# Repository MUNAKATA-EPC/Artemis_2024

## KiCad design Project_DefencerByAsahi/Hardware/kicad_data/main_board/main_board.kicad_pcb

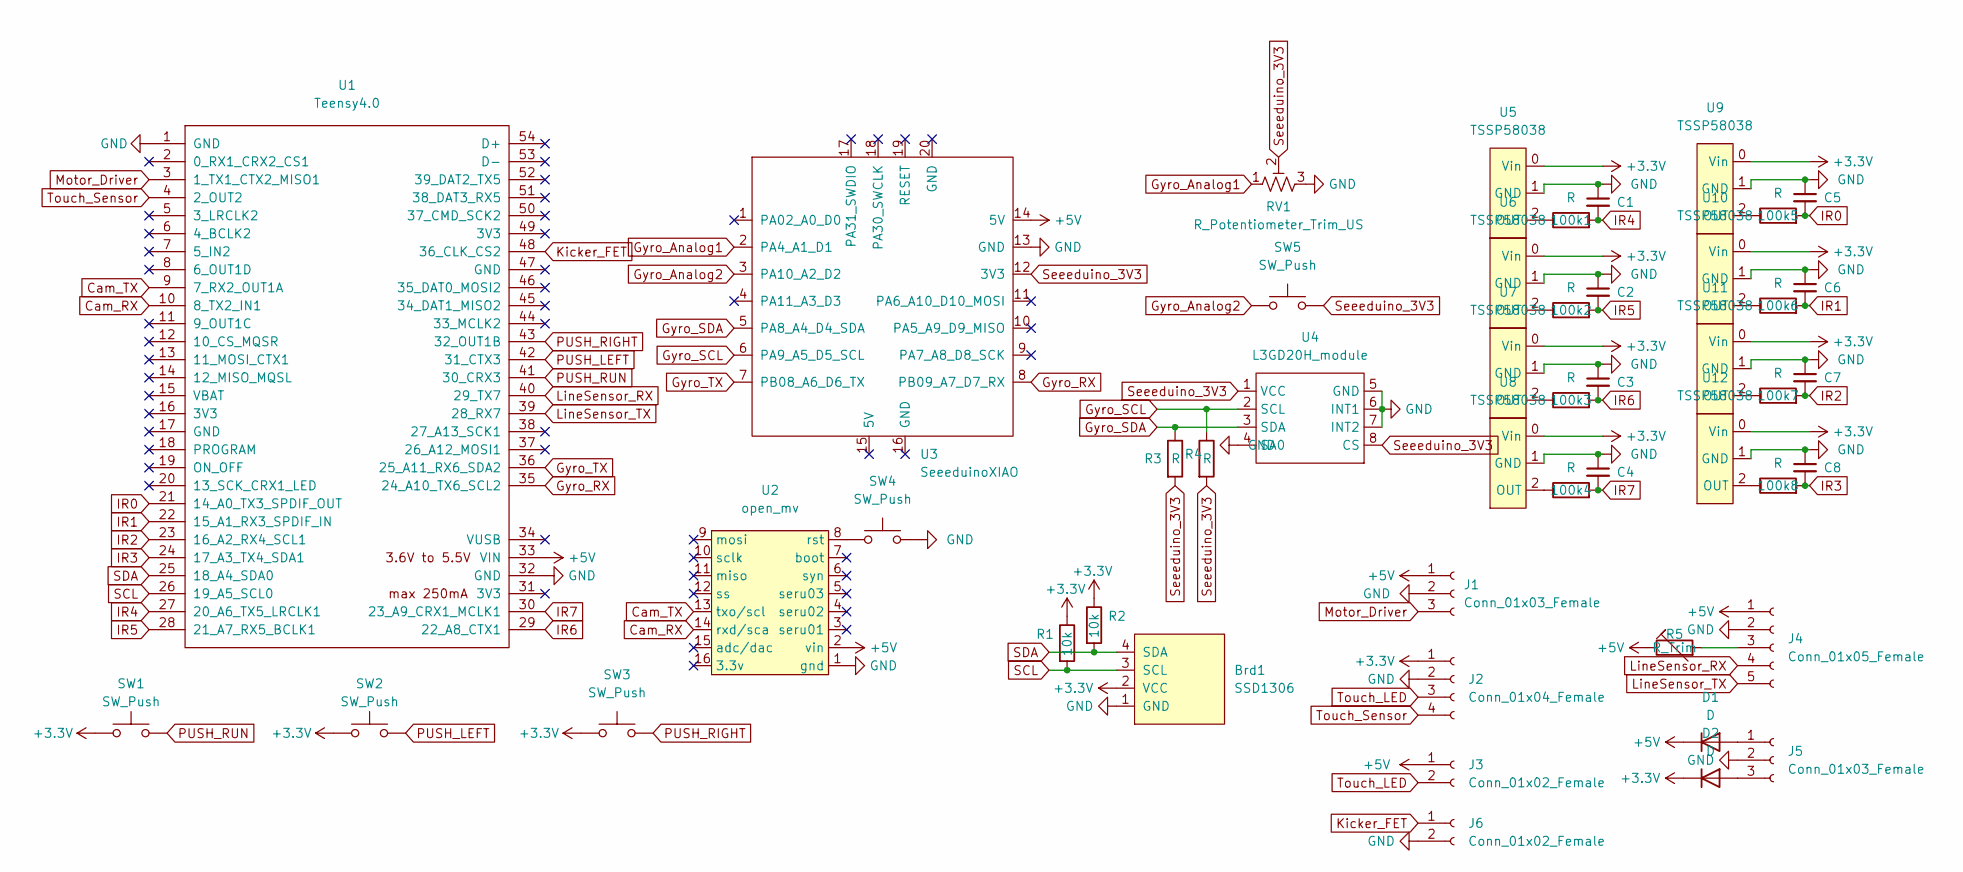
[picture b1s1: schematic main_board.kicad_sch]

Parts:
100k1, 100k2, 100k3, 100k4, 100k5, 100k6, 100k7, 100k8: R; R_Axial_DIN0204_L3.6mm_D1.6mm_P5.08mm_Horizontal
Brd1: SSD1306; 128x64OLED
C1, C2, C3, C4, C5, C6, C7, C8: C_Small; C_Disc_D3.0mm_W2.0mm_P2.50mm
D1, D2: D; D_A-405_P7.62mm_Horizontal
J1, J5: Conn_01x03_Female; JST_XH_B3B-XH-A_1x03_P2.50mm_Vertical
J2: Conn_01x04_Female; JST_XH_B4B-XH-A_1x04_P2.50mm_Vertical
J3, J6: Conn_01x02_Female; JST_XH_B2B-XH-A_1x02_P2.50mm_Vertical
J4: Conn_01x05_Female; JST_XH_B5B-XH-A_1x05_P2.50mm_Vertical
R1, R2: 10k; R_Axial_DIN0204_L3.6mm_D1.6mm_P5.08mm_Horizontal
R3, R4: R; R_Axial_DIN0204_L3.6mm_D1.6mm_P5.08mm_Horizontal
R5: R_Trim; R_Varlable
RV1: R_Potentiometer_Trim_US; R_Varlable
SW1, SW2, SW3, SW4, SW5: SW_Push; SW_PUSH_6mm_H5mm
U1: Teensy4.0; Teensy_Brakeout
U2: open_mv; OpenMV
U3: SeeeduinoXIAO; seeeduinoXIAO
U4: L3GD20H_module; L3GD20H_Module_KiCad6.0
U5, U6, U7, U8, U9, U10, U11, U12: TSSP58038

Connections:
+3.3V: Brd1.2 (VCC), D2.1 (K), J2.1, R1.1, R2.1, SW1.1, SW2.1, SW3.1, U5.0 (Vin), U6.0 (Vin), U7.0 (Vin), U8.0 (Vin), U9.0 (Vin), U10.0 (Vin), U11.0 (Vin), U12.0 (Vin)
+5V: D1.1 (K), J1.1, J3.1, J4.1, R5.1, U1.33 (VIN), U2.2 (vin), U3.14 (5V)
Cam_RX: U1.10 (8_TX2_IN1), U2.14 (rxd/sca)
Cam_TX: U1.9 (7_RX2_OUT1A), U2.13 (txo/scl)
GND: Brd1.1 (GND), C1.1, C2.1, C3.1, C4.1, C5.1, C6.1, C7.1, C8.1, J1.2, J2.2, J4.2, J5.2, J6.2, RV1.3, SW4.2, U1.1 (GND), U1.32 (GND), U2.1 (gnd), U3.13 (GND), U4.4 (SA0), U4.5 (GND), U4.6 (INT1), U4.7 (INT2), U5.1 (GND), U6.1 (GND), U7.1 (GND), U8.1 (GND), U9.1 (GND), U10.1 (GND), U11.1 (GND), U12.1 (GND)
Gyro_Analog1: RV1.1, U3.2 (PA4_A1_D1)
Gyro_Analog2: SW5.1, U3.3 (PA10_A2_D2)
Gyro_RX: U1.35 (24_A10_TX6_SCL2), U3.8 (PB09_A7_D7_RX)
Gyro_SCL: R4.1, U3.6 (PA9_A5_D5_SCL), U4.2 (SCL)
Gyro_SDA: R3.1, U3.5 (PA8_A4_D4_SDA), U4.3 (SDA)
Gyro_TX: U1.36 (25_A11_RX6_SDA2), U3.7 (PB08_A6_D6_TX)
IR0: 100k5.2, C5.2, U1.21 (14_A0_TX3_SPDIF_OUT)
IR1: 100k6.2, C6.2, U1.22 (15_A1_RX3_SPDIF_IN)
IR2: 100k7.2, C7.2, U1.23 (16_A2_RX4_SCL1)
IR3: 100k8.2, C8.2, U1.24 (17_A3_TX4_SDA1)
IR4: 100k1.2, C1.2, U1.27 (20_A6_TX5_LRCLK1)
IR5: 100k2.2, C2.2, U1.28 (21_A7_RX5_BCLK1)
IR6: 100k3.2, C3.2, U1.29 (22_A8_CTX1)
IR7: 100k4.2, C4.2, U1.30 (23_A9_CRX1_MCLK1)
Kicker_FET: J6.1, U1.48 (36_CLK_CS2)
LineSensor_RX: J4.4, U1.40 (29_TX7)
LineSensor_TX: J4.5, U1.39 (28_RX7)
Motor_Driver: J1.3, U1.3 (1_TX1_CTX2_MISO1)
unnamed: 100k1.1, U5.2 (OUT)
unnamed: 100k2.1, U6.2 (OUT)
unnamed: 100k3.1, U7.2 (OUT)
unnamed: 100k4.1, U8.2 (OUT)
unnamed: 100k5.1, U9.2 (OUT)
unnamed: 100k6.1, U10.2 (OUT)
unnamed: 100k7.1, U11.2 (OUT)
unnamed: 100k8.1, U12.2 (OUT)
unnamed: D1.2 (A), J5.1
unnamed: D2.2 (A), J5.3
unnamed: J4.3, R5.2
unnamed: SW4.1, U2.8 (rst)
PUSH_LEFT: SW2.2, U1.42 (31_CTX3)
PUSH_RIGHT: SW3.2, U1.43 (32_OUT1B)
PUSH_RUN: SW1.2, U1.41 (30_CRX3)
SCL: Brd1.3 (SCL), R1.2, U1.26 (19_A5_SCL0)
SDA: Brd1.4 (SDA), R2.2, U1.25 (18_A4_SDA0)
Seeeduino_3V3: R3.2, R4.2, RV1.2, SW5.2, U3.12 (3V3), U4.1 (VCC), U4.8 (CS)
Touch_LED: J2.3, J3.2
Touch_Sensor: J2.4, U1.4 (2_OUT2)

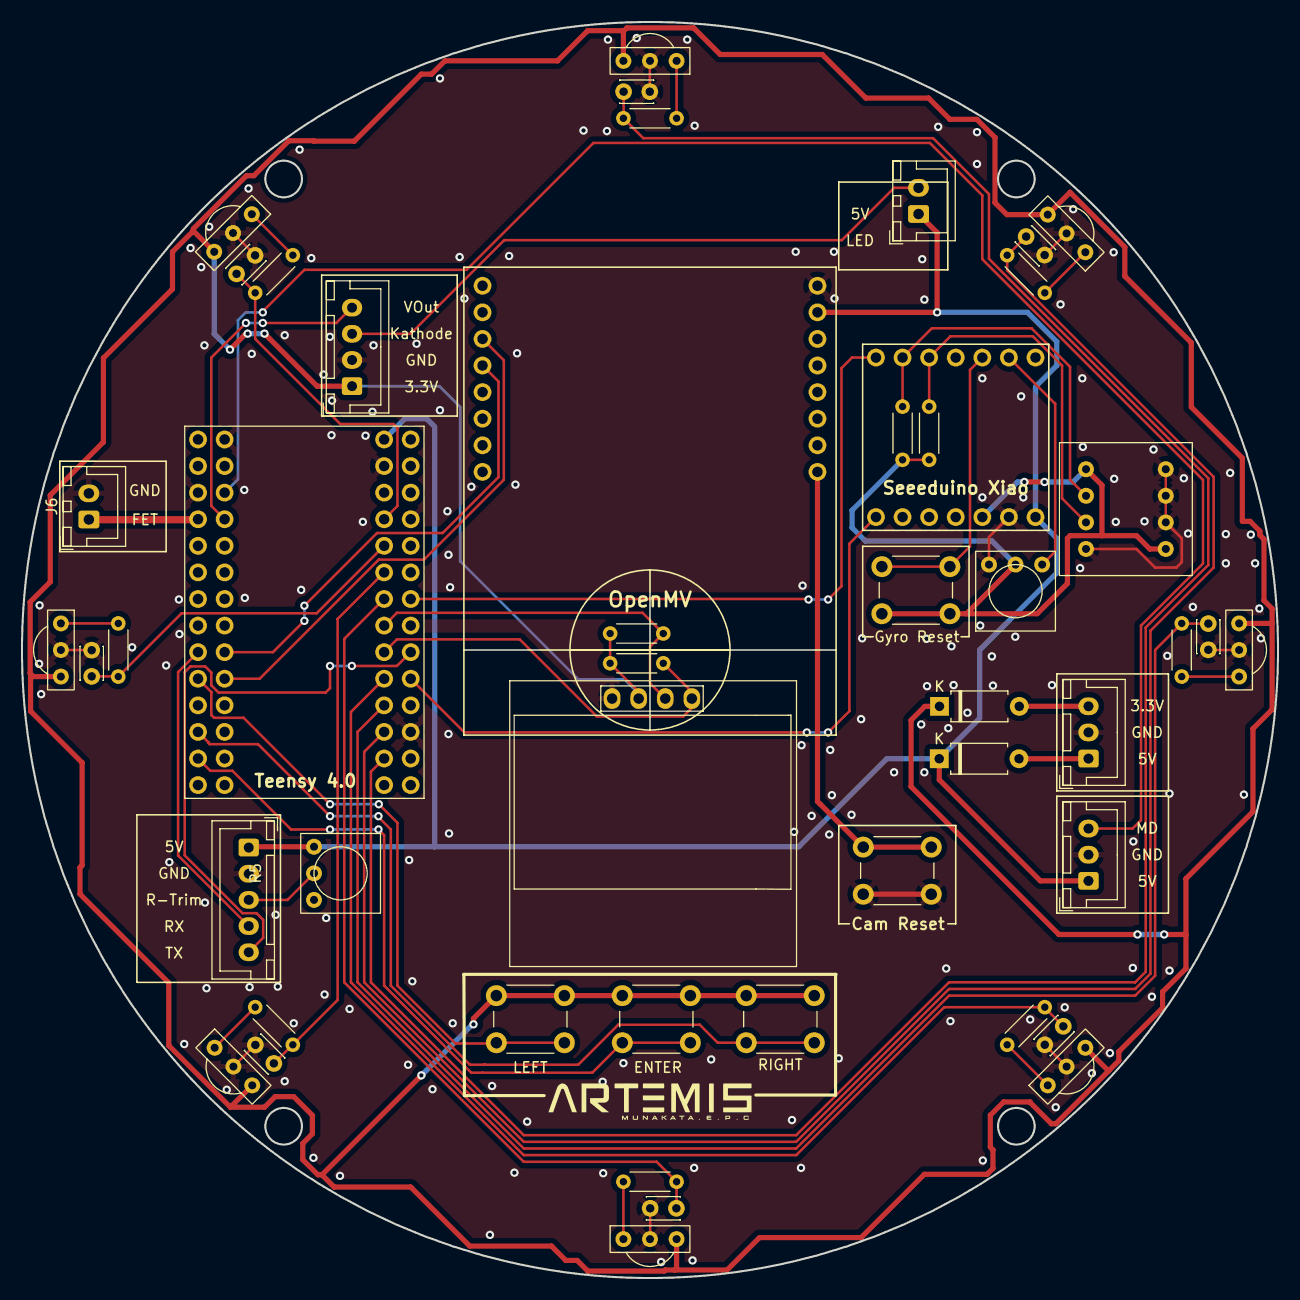
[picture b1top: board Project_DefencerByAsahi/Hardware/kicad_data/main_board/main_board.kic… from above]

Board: 2 copper layers, 120.0 x 120.0 mm, 48 parts (0 on the bottom side), 43 nets.

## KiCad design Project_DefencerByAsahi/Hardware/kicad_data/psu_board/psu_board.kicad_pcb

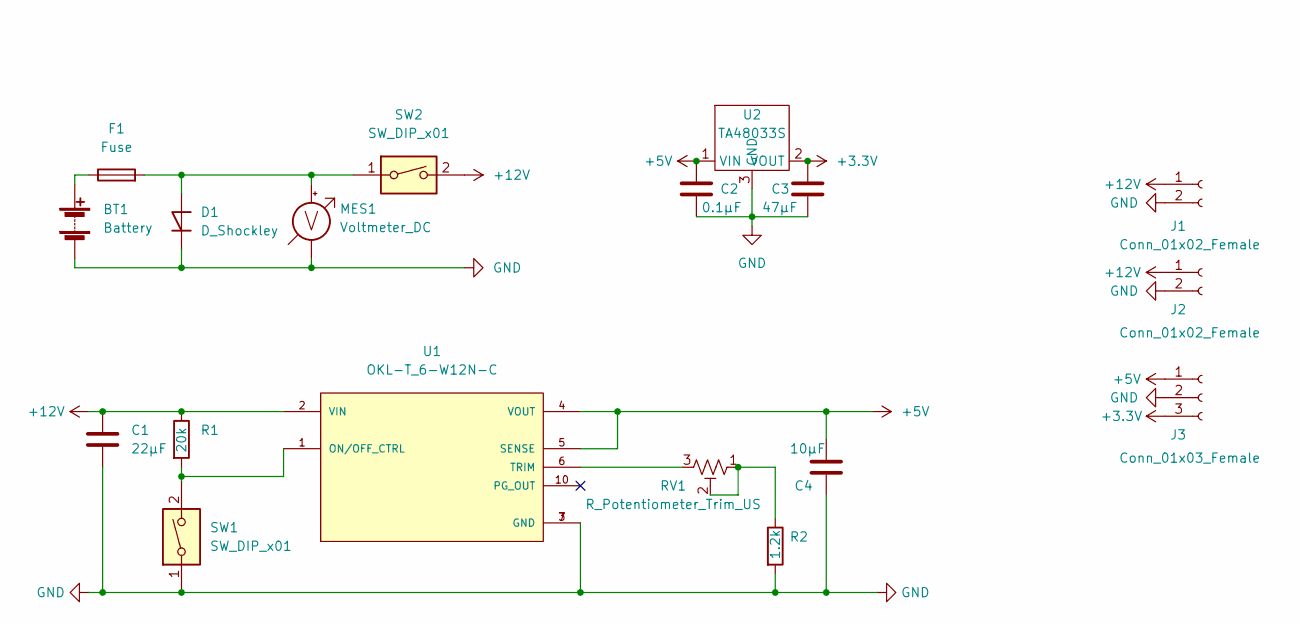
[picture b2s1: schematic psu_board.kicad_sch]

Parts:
BT1: Battery; JST_VH_B2P-VH-B_1x02_P3.96mm_Vertical
C1: 22μF; C_Disc_D5.1mm_W3.2mm_P5.00mm
C2: 0.1μF; C_Disc_D3.0mm_W1.6mm_P2.50mm
C3: 47μF; C_Radial_D6.3mm_H11.0mm_P2.50mm
C4: 10μF; C_Disc_D5.1mm_W3.2mm_P5.00mm
D1: D_Shockley; D_5W_P12.70mm_Horizontal
F1: Fuse; fuse_socket
J1, J2: Conn_01x02_Female; JST_XH_B2B-XH-A_1x02_P2.50mm_Vertical
J3: Conn_01x03_Female; JST_XH_B3B-XH-A_1x03_P2.50mm_Vertical
MES1: Voltmeter_DC; voltage_counter
R1: 20k; R_Axial_DIN0204_L3.6mm_D1.6mm_P5.08mm_Horizontal
R2: 1.2k; R_Axial_DIN0204_L3.6mm_D1.6mm_P5.08mm_Horizontal
RV1: R_Potentiometer_Trim_US; Potentiometer_Bourns_3296W_Vertical
SW1, SW2: SW_DIP_x01; DS-850k
U1: OKL-T_6-W12N-C; DCDC-murata-6A
U2: TA48033S

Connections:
+3.3V: C3.1, J3.3, U2.2 (VOUT)
+5V: C2.1, C4.1, J3.1, U1.4 (VOUT), U1.5 (SENSE), U2.1 (VIN)
+12V: C1.1, J1.1, J2.1, R1.1, SW2.2, U1.2 (VIN)
GND: BT1.2 (-), C1.2, C2.2, C3.2, C4.2, D1.1 (K), J1.2, J2.2, J3.2, MES1.1 (-), R2.2, SW1.1, U1.3 (GND), U1.7 (GND), U2.3 (GND)
unnamed: BT1.1 (+), F1.1
unnamed: D1.2 (A), F1.2, MES1.2 (+), SW2.1
unnamed: R1.2, SW1.2, U1.1 (ON/OFF_CTRL)
unnamed: R2.1, RV1.1, RV1.2
unnamed: RV1.3, U1.6 (TRIM)

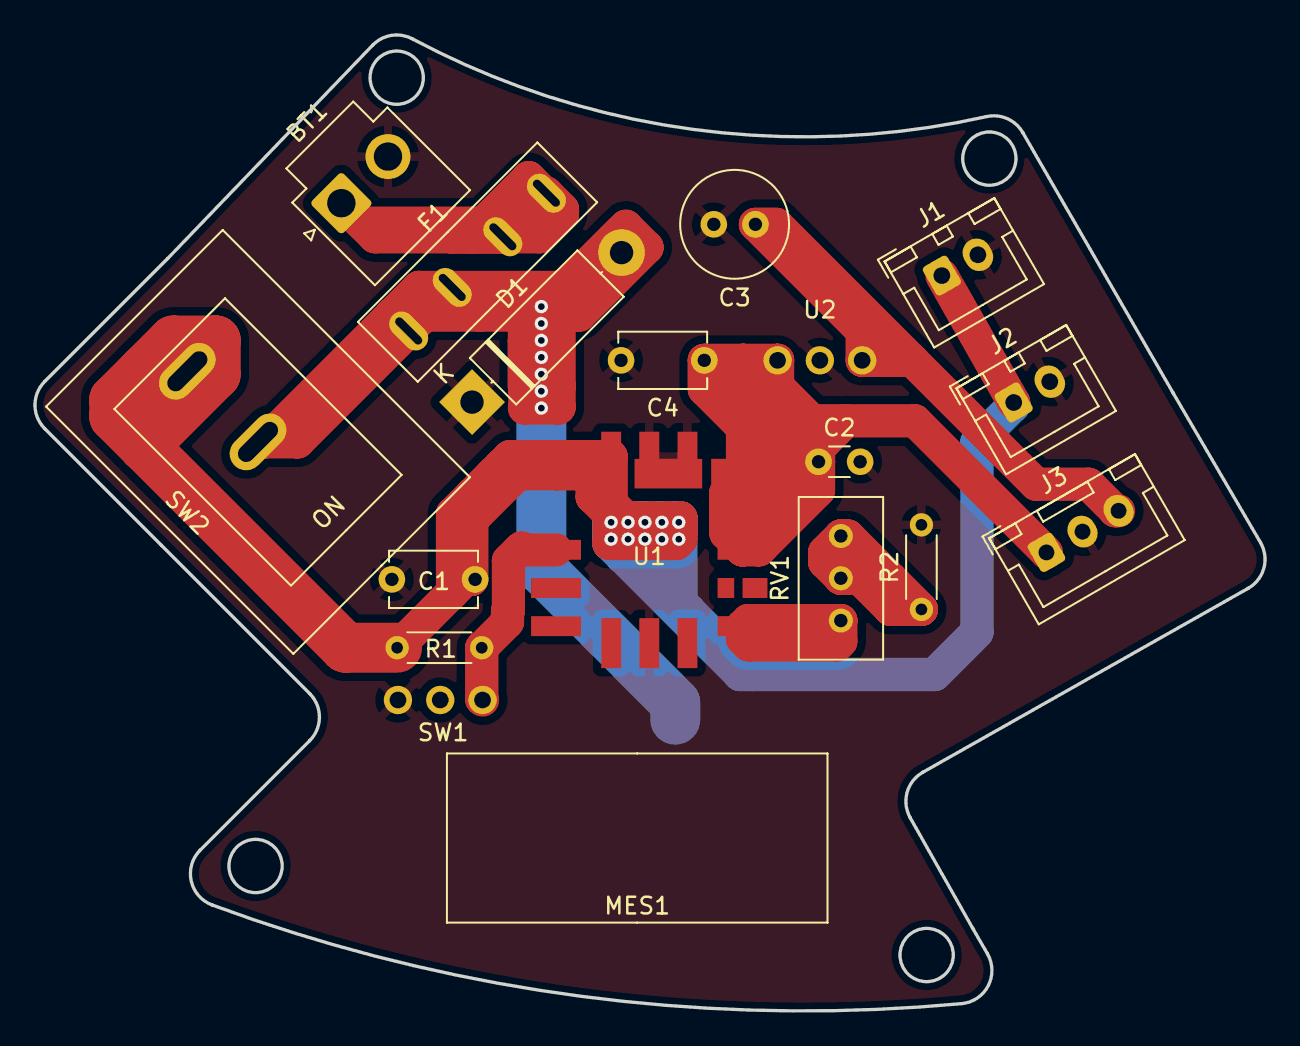
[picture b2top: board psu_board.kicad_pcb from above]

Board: 2 copper layers, 73.9 x 58.6 mm, 18 parts (0 on the bottom side), 9 nets.

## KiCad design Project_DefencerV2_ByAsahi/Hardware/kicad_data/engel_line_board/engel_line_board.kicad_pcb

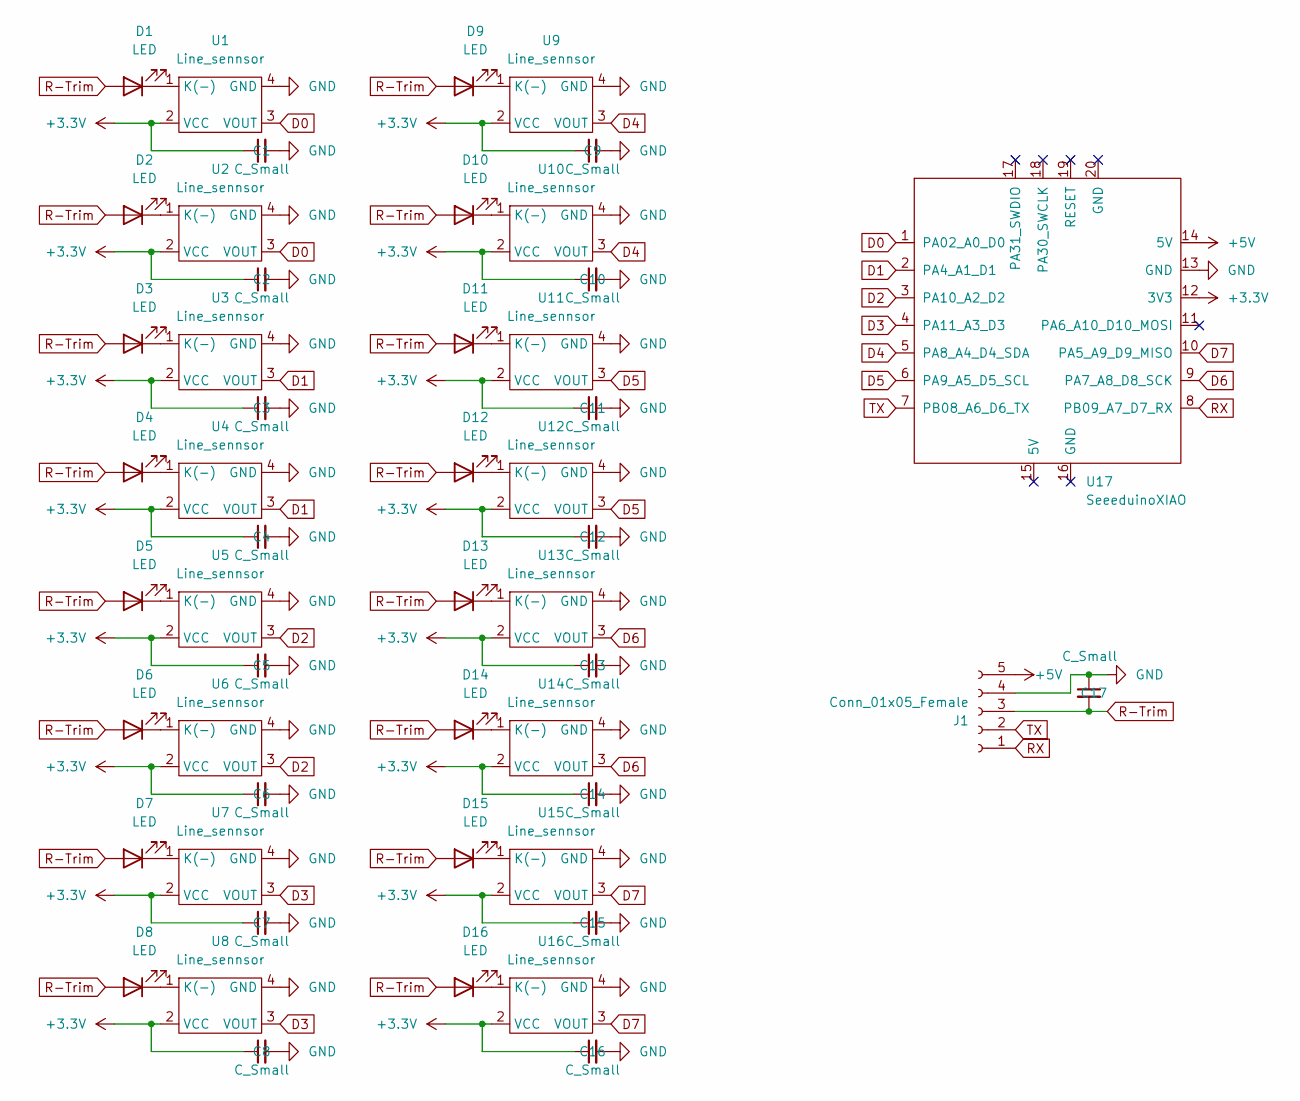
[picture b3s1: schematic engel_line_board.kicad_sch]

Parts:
C1, C2, C3, C4, C5, C6, C7, C8, C9, C10, C11, C12, C13, C14, C15, C16, C17: C_Small; C_Disc_D3.8mm_W2.6mm_P2.50mm
D1, D2, D3, D4, D5, D6, D7, D8, D9, D10, D11, D12, D13, D14, D15, D16: LED; LED_D3.0mm_Clear
J1: Conn_01x05_Female; JST_XH_S5B-XH-A_1x05_P2.50mm_Horizontal
U1, U2, U3, U4, U5, U6, U7, U8, U9, U10, U11, U12, U13, U14, U15, U16: Line_sennsor; Line_Sensor
U17: SeeeduinoXIAO; seeeduinoXIAO

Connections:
+3.3V: C1.1, C2.1, C3.1, C4.1, C5.1, C6.1, C7.1, C8.1, C9.1, C10.1, C11.1, C12.1, C13.1, C14.1, C15.1, C16.1, U1.2 (VCC), U2.2 (VCC), U3.2 (VCC), U4.2 (VCC), U5.2 (VCC), U6.2 (VCC), U7.2 (VCC), U8.2 (VCC), U9.2 (VCC), U10.2 (VCC), U11.2 (VCC), U12.2 (VCC), U13.2 (VCC), U14.2 (VCC), U15.2 (VCC), U16.2 (VCC), U17.12 (3V3)
+5V: J1.5, U17.14 (5V)
D0: U1.3 (VOUT), U2.3 (VOUT), U17.1 (PA02_A0_D0)
D1: U3.3 (VOUT), U4.3 (VOUT), U17.2 (PA4_A1_D1)
D2: U5.3 (VOUT), U6.3 (VOUT), U17.3 (PA10_A2_D2)
D3: U7.3 (VOUT), U8.3 (VOUT), U17.4 (PA11_A3_D3)
D4: U9.3 (VOUT), U10.3 (VOUT), U17.5 (PA8_A4_D4_SDA)
D5: U11.3 (VOUT), U12.3 (VOUT), U17.6 (PA9_A5_D5_SCL)
D6: U13.3 (VOUT), U14.3 (VOUT), U17.9 (PA7_A8_D8_SCK)
D7: U15.3 (VOUT), U16.3 (VOUT), U17.10 (PA5_A9_D9_MISO)
GND: C1.2, C2.2, C3.2, C4.2, C5.2, C6.2, C7.2, C8.2, C9.2, C10.2, C11.2, C12.2, C13.2, C14.2, C15.2, C16.2, C17.1, J1.4, U1.4 (GND), U2.4 (GND), U3.4 (GND), U4.4 (GND), U5.4 (GND), U6.4 (GND), U7.4 (GND), U8.4 (GND), U9.4 (GND), U10.4 (GND), U11.4 (GND), U12.4 (GND), U13.4 (GND), U14.4 (GND), U15.4 (GND), U16.4 (GND), U17.13 (GND)
unnamed: D1.1 (K), U1.1 (K(-))
unnamed: D2.1 (K), U2.1 (K(-))
unnamed: D3.1 (K), U3.1 (K(-))
unnamed: D4.1 (K), U4.1 (K(-))
unnamed: D5.1 (K), U5.1 (K(-))
unnamed: D6.1 (K), U6.1 (K(-))
unnamed: D7.1 (K), U7.1 (K(-))
unnamed: D8.1 (K), U8.1 (K(-))
unnamed: D9.1 (K), U9.1 (K(-))
unnamed: D10.1 (K), U10.1 (K(-))
unnamed: D11.1 (K), U11.1 (K(-))
unnamed: D12.1 (K), U12.1 (K(-))
unnamed: D13.1 (K), U13.1 (K(-))
unnamed: D14.1 (K), U14.1 (K(-))
unnamed: D15.1 (K), U15.1 (K(-))
unnamed: D16.1 (K), U16.1 (K(-))
R-Trim: C17.2, D1.2 (A), D2.2 (A), D3.2 (A), D4.2 (A), D5.2 (A), D6.2 (A), D7.2 (A), D8.2 (A), D9.2 (A), D10.2 (A), D11.2 (A), D12.2 (A), D13.2 (A), D14.2 (A), D15.2 (A), D16.2 (A), J1.3
RX: J1.1, U17.8 (PB09_A7_D7_RX)
TX: J1.2, U17.7 (PB08_A6_D6_TX)

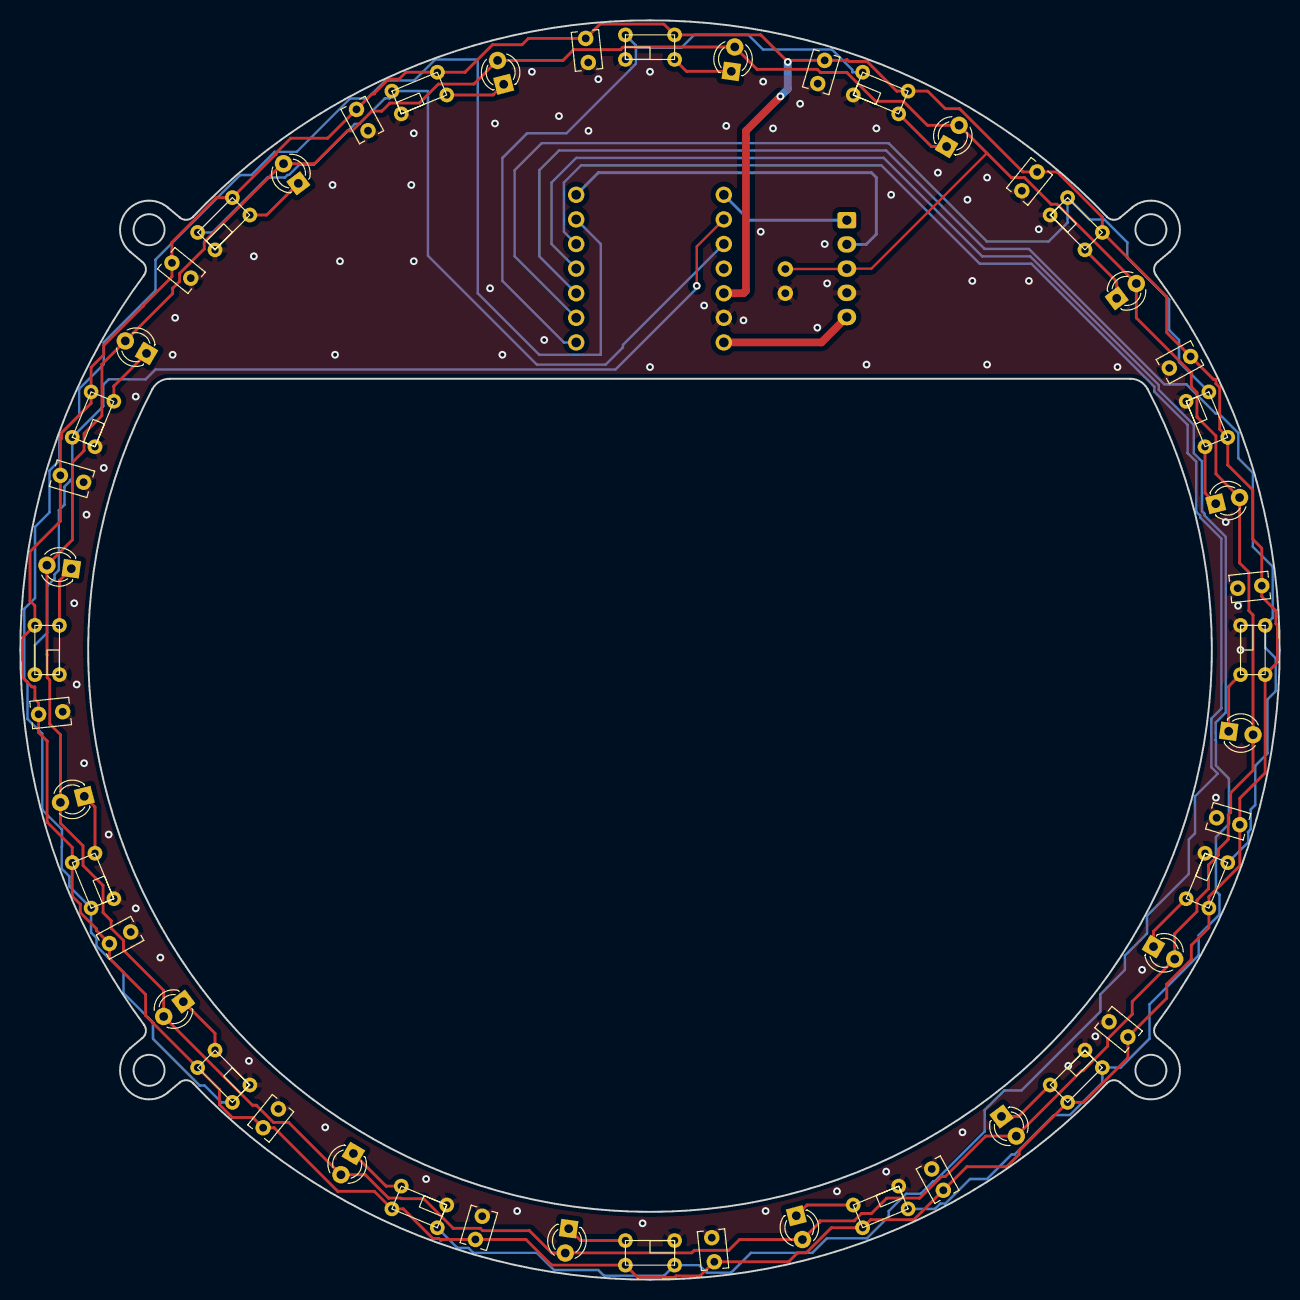
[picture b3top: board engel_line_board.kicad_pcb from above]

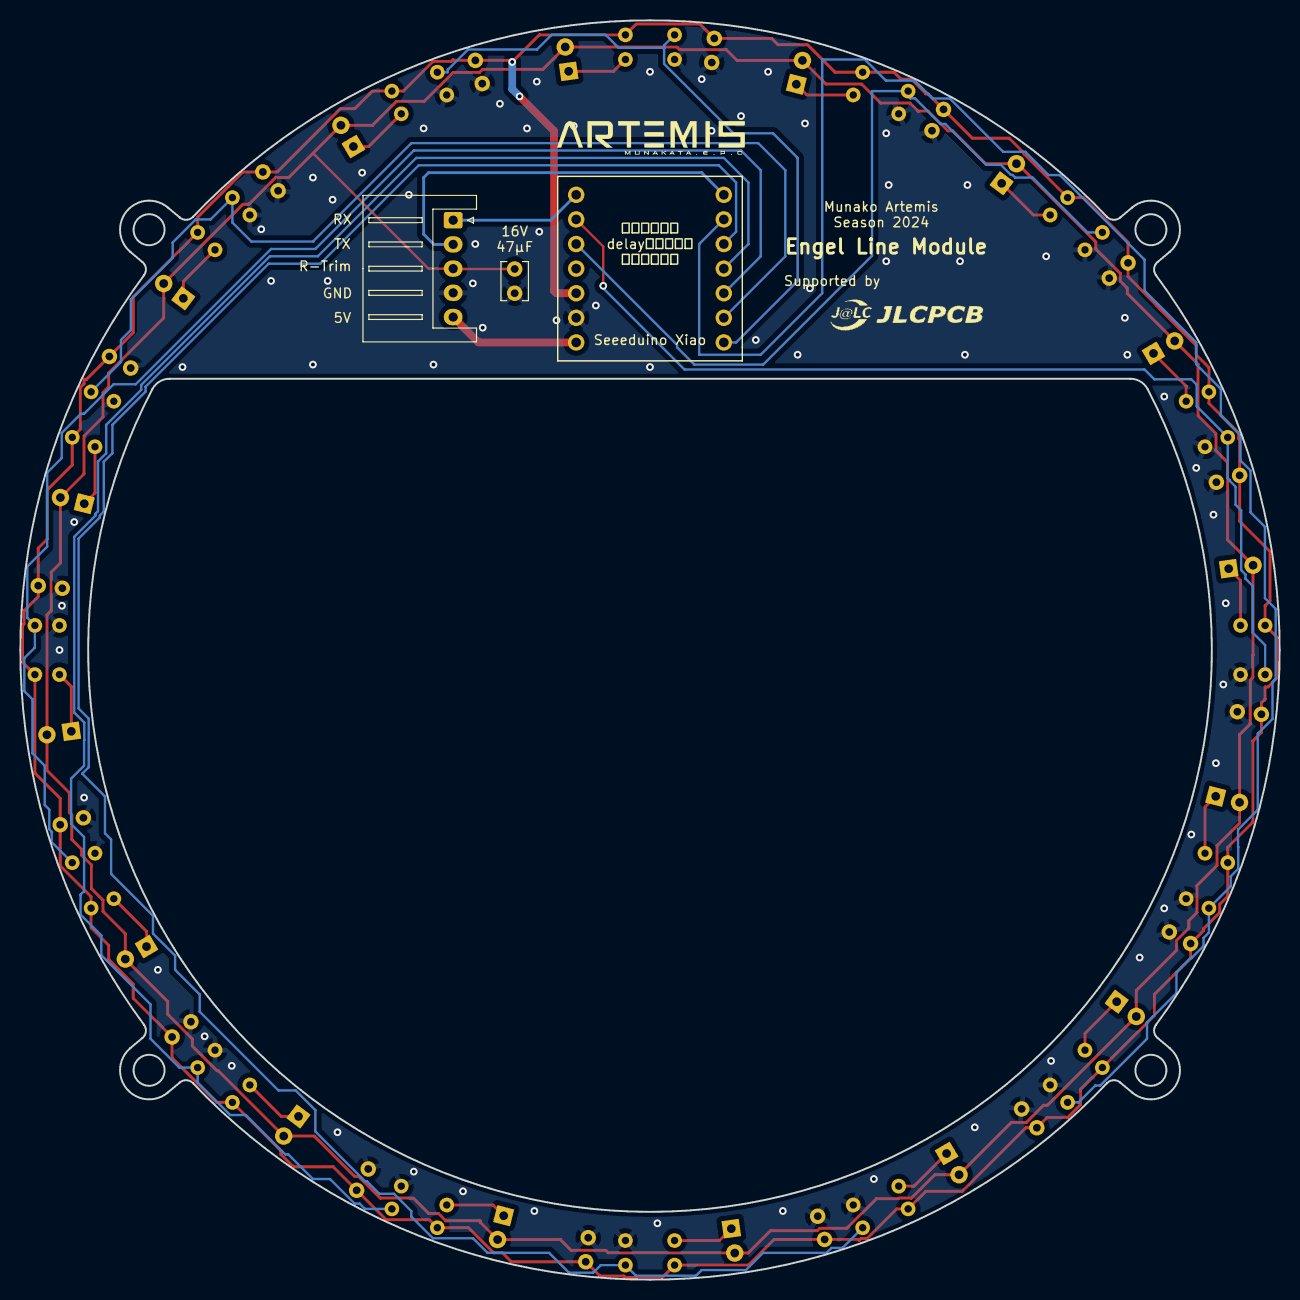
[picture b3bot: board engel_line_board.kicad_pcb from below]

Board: 2 copper layers, 130.0 x 130.0 mm, 51 parts (3 on the bottom side), 30 nets.

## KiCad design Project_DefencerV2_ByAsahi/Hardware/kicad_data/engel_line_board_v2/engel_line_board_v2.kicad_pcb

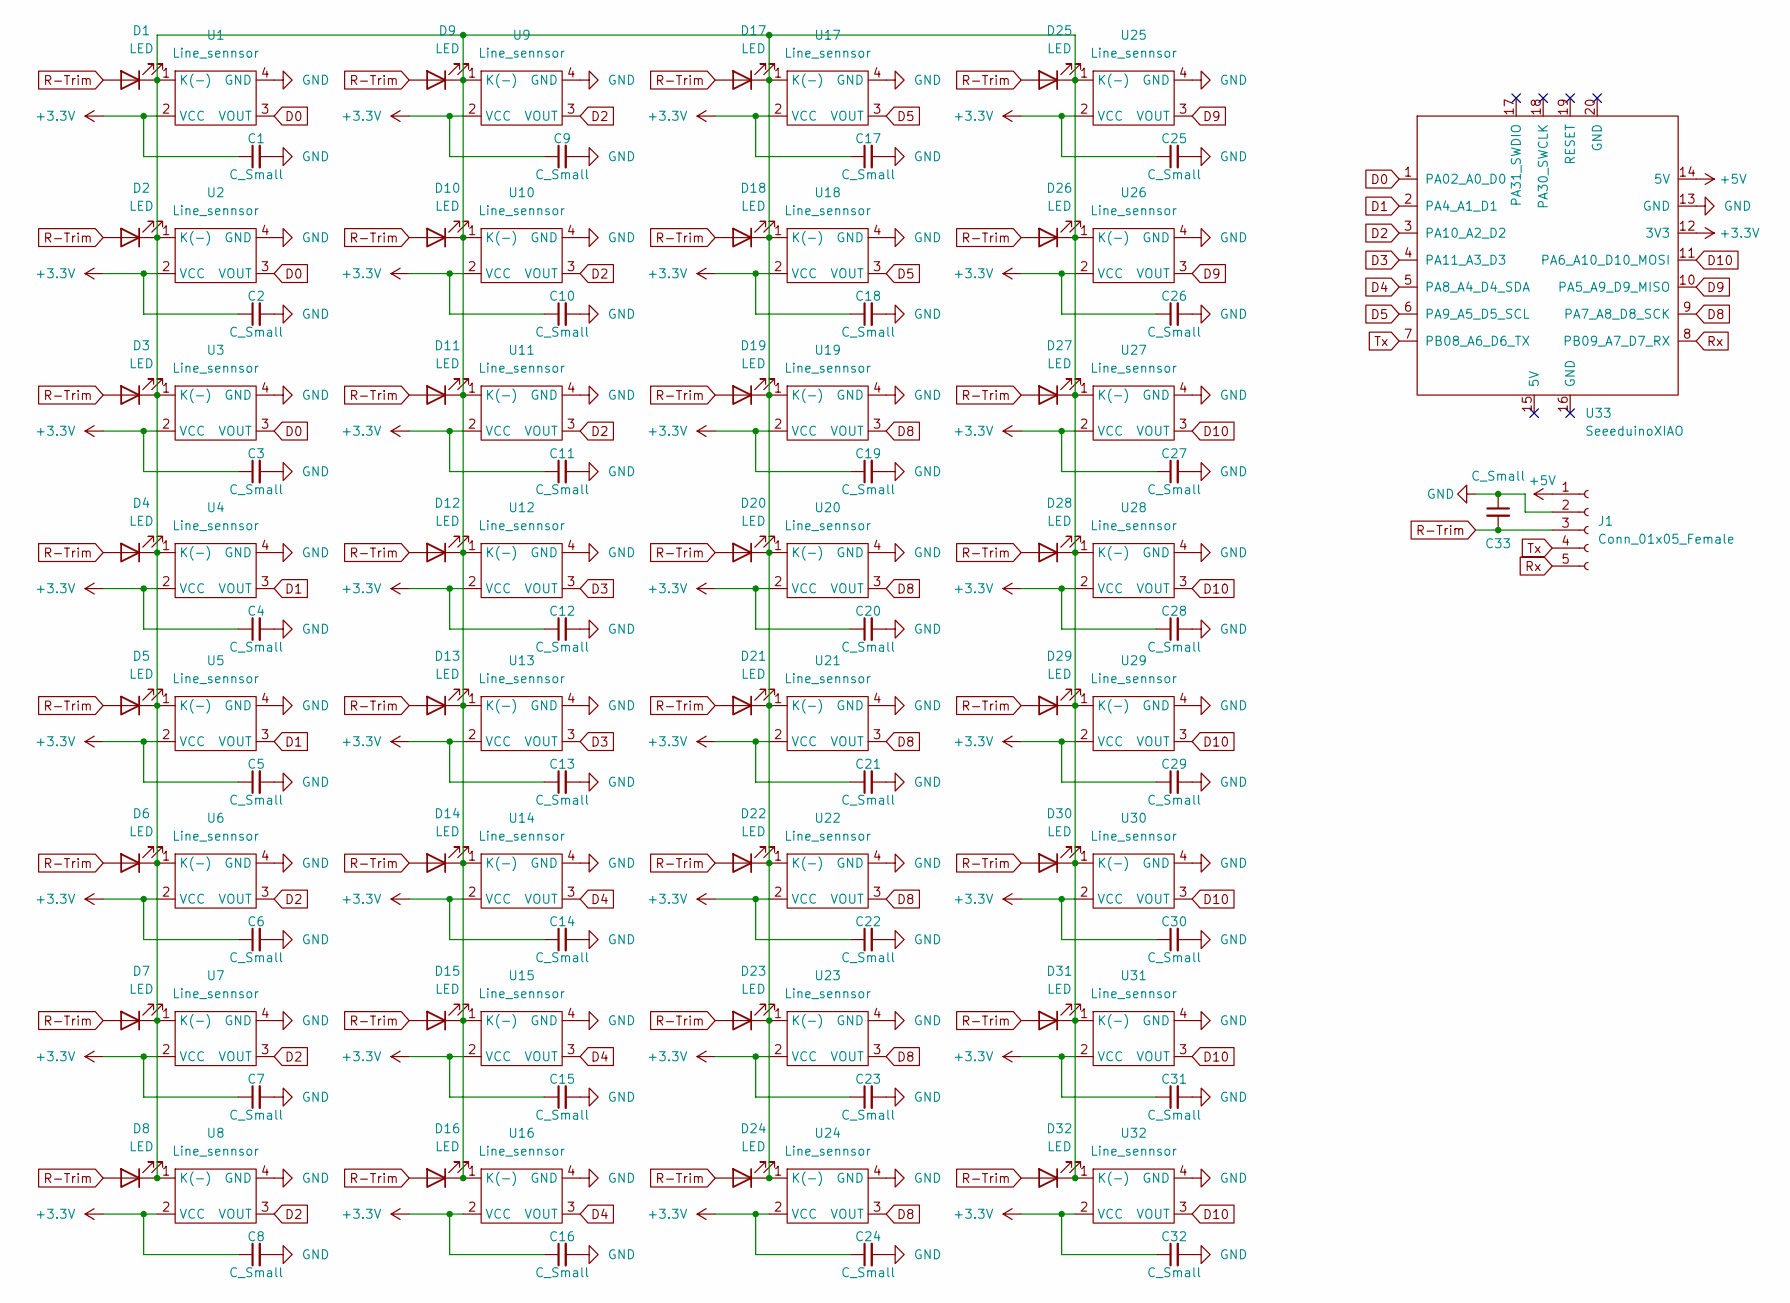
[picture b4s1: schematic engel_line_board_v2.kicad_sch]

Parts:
C1, C2, C3, C4, C5, C6, C7, C8, C9, C10, C11, C12, C13, C14, C15, C16, C17, C18, C19, C20, C21, C22, C23, C24, C25, C26, C27, C28, C29, C30, C31, C32: C_Small; C_Disc_D3.8mm_W2.6mm_P2.50mm
C33: C_Small; CP_Radial_D5.0mm_P2.50mm
D1, D2, D3, D4, D5, D6, D7, D8, D9, D10, D11, D12, D13, D14, D15, D16, D17, D18, D19, D20, D21, D22, D23, D24, D25, D26, D27, D28, D29, D30, D31, D32: LED; LED_D3.0mm_Clear
J1: Conn_01x05_Female; JST_XH_S5B-XH-A_1x05_P2.50mm_Horizontal
U1, U2, U3, U4, U5, U6, U7, U8, U9, U10, U11, U12, U13, U14, U15, U16, U17, U18, U19, U20, U21, U22, U23, U24, U25, U26, U27, U28, U29, U30, U31, U32: Line_sennsor; Line_Sensor_SMD
U33: SeeeduinoXIAO; seeeduinoXIAO

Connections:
+3.3V: C1.1, C2.1, C3.1, C4.1, C5.1, C6.1, C7.1, C8.1, C9.1, C10.1, C11.1, C12.1, C13.1, C14.1, C15.1, C16.1, C17.1, C18.1, C19.1, C20.1, C21.1, C22.1, C23.1, C24.1, C25.1, C26.1, C27.1, C28.1, C29.1, C30.1, C31.1, C32.1, U1.2 (VCC), U2.2 (VCC), U3.2 (VCC), U4.2 (VCC), U5.2 (VCC), U6.2 (VCC), U7.2 (VCC), U8.2 (VCC), U9.2 (VCC), U10.2 (VCC), U11.2 (VCC), U12.2 (VCC), U13.2 (VCC), U14.2 (VCC), U15.2 (VCC), U16.2 (VCC), U17.2 (VCC), U18.2 (VCC), U19.2 (VCC), U20.2 (VCC), U21.2 (VCC), U22.2 (VCC), U23.2 (VCC), U24.2 (VCC), U25.2 (VCC), U26.2 (VCC), U27.2 (VCC), U28.2 (VCC), U29.2 (VCC), U30.2 (VCC), U31.2 (VCC), U32.2 (VCC), U33.12 (3V3)
+5V: J1.1, U33.14 (5V)
D0: U1.3 (VOUT), U2.3 (VOUT), U3.3 (VOUT), U33.1 (PA02_A0_D0)
D1: U4.3 (VOUT), U5.3 (VOUT), U33.2 (PA4_A1_D1)
D2: U6.3 (VOUT), U7.3 (VOUT), U8.3 (VOUT), U9.3 (VOUT), U10.3 (VOUT), U11.3 (VOUT), U33.3 (PA10_A2_D2)
D3: U12.3 (VOUT), U13.3 (VOUT), U33.4 (PA11_A3_D3)
D4: U14.3 (VOUT), U15.3 (VOUT), U16.3 (VOUT), U33.5 (PA8_A4_D4_SDA)
D5: U17.3 (VOUT), U18.3 (VOUT), U33.6 (PA9_A5_D5_SCL)
D8: U19.3 (VOUT), U20.3 (VOUT), U21.3 (VOUT), U22.3 (VOUT), U23.3 (VOUT), U24.3 (VOUT), U33.9 (PA7_A8_D8_SCK)
D9: U25.3 (VOUT), U26.3 (VOUT), U33.10 (PA5_A9_D9_MISO)
D10: U27.3 (VOUT), U28.3 (VOUT), U29.3 (VOUT), U30.3 (VOUT), U31.3 (VOUT), U32.3 (VOUT), U33.11 (PA6_A10_D10_MOSI)
GND: C1.2, C2.2, C3.2, C4.2, C5.2, C6.2, C7.2, C8.2, C9.2, C10.2, C11.2, C12.2, C13.2, C14.2, C15.2, C16.2, C17.2, C18.2, C19.2, C20.2, C21.2, C22.2, C23.2, C24.2, C25.2, C26.2, C27.2, C28.2, C29.2, C30.2, C31.2, C32.2, C33.1, J1.2, U1.4 (GND), U2.4 (GND), U3.4 (GND), U4.4 (GND), U5.4 (GND), U6.4 (GND), U7.4 (GND), U8.4 (GND), U9.4 (GND), U10.4 (GND), U11.4 (GND), U12.4 (GND), U13.4 (GND), U14.4 (GND), U15.4 (GND), U16.4 (GND), U17.4 (GND), U18.4 (GND), U19.4 (GND), U20.4 (GND), U21.4 (GND), U22.4 (GND), U23.4 (GND), U24.4 (GND), U25.4 (GND), U26.4 (GND), U27.4 (GND), U28.4 (GND), U29.4 (GND), U30.4 (GND), U31.4 (GND), U32.4 (GND), U33.13 (GND)
unnamed: D1.1 (K), D2.1 (K), D3.1 (K), D4.1 (K), D5.1 (K), D6.1 (K), D7.1 (K), D8.1 (K), D9.1 (K), D10.1 (K), D11.1 (K), D12.1 (K), D13.1 (K), D14.1 (K), D15.1 (K), D16.1 (K), D17.1 (K), D18.1 (K), D19.1 (K), D20.1 (K), D21.1 (K), D22.1 (K), D23.1 (K), D24.1 (K), D25.1 (K), D26.1 (K), D27.1 (K), D28.1 (K), D29.1 (K), D30.1 (K), D31.1 (K), D32.1 (K), U1.1 (K(-)), U2.1 (K(-)), U3.1 (K(-)), U4.1 (K(-)), U5.1 (K(-)), U6.1 (K(-)), U7.1 (K(-)), U8.1 (K(-)), U9.1 (K(-)), U10.1 (K(-)), U11.1 (K(-)), U12.1 (K(-)), U13.1 (K(-)), U14.1 (K(-)), U15.1 (K(-)), U16.1 (K(-)), U17.1 (K(-)), U18.1 (K(-)), U19.1 (K(-)), U20.1 (K(-)), U21.1 (K(-)), U22.1 (K(-)), U23.1 (K(-)), U24.1 (K(-)), U25.1 (K(-)), U26.1 (K(-)), U27.1 (K(-)), U28.1 (K(-)), U29.1 (K(-)), U30.1 (K(-)), U31.1 (K(-)), U32.1 (K(-))
R-Trim: C33.2, D1.2 (A), D2.2 (A), D3.2 (A), D4.2 (A), D5.2 (A), D6.2 (A), D7.2 (A), D8.2 (A), D9.2 (A), D10.2 (A), D11.2 (A), D12.2 (A), D13.2 (A), D14.2 (A), D15.2 (A), D16.2 (A), D17.2 (A), D18.2 (A), D19.2 (A), D20.2 (A), D21.2 (A), D22.2 (A), D23.2 (A), D24.2 (A), D25.2 (A), D26.2 (A), D27.2 (A), D28.2 (A), D29.2 (A), D30.2 (A), D31.2 (A), D32.2 (A), J1.3
Rx: J1.5, U33.8 (PB09_A7_D7_RX)
Tx: J1.4, U33.7 (PB08_A6_D6_TX)

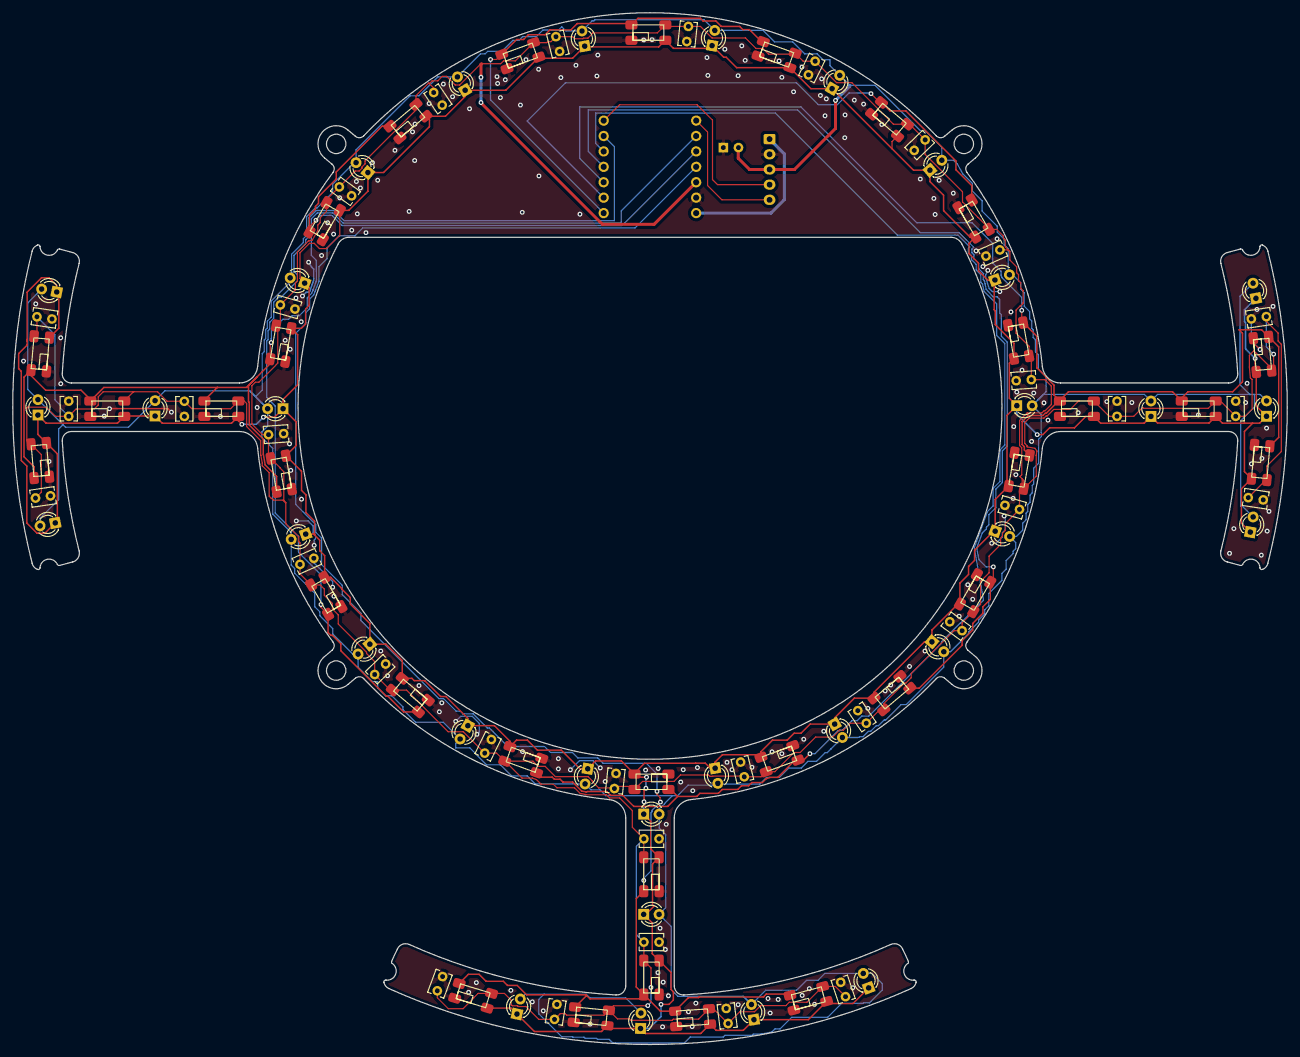
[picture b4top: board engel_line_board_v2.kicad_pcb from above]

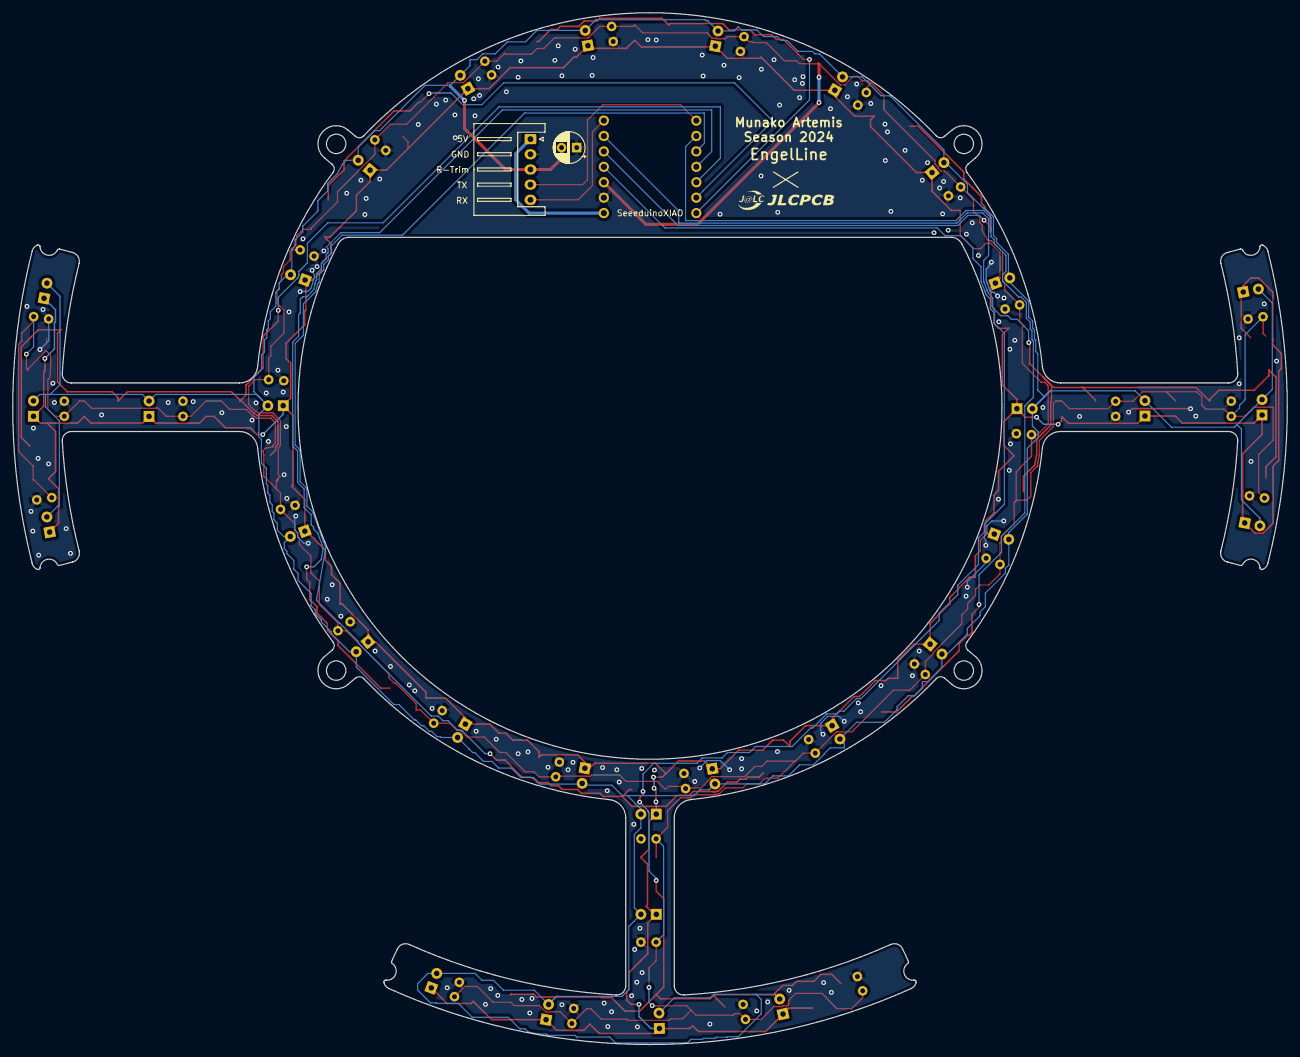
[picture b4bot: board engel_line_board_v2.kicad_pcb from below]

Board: 2 copper layers, 210.0 x 170.0 mm, 99 parts (3 on the bottom side), 16 nets.
